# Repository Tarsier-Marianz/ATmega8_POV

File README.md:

# ATmega8-POV

A simple persistence-of-vision (POV) display with ATmega8 microcontroller

### Thanks

[KiCad IDE](http://kicad-pcb.org/) - for letting me use a free software in designing PCB

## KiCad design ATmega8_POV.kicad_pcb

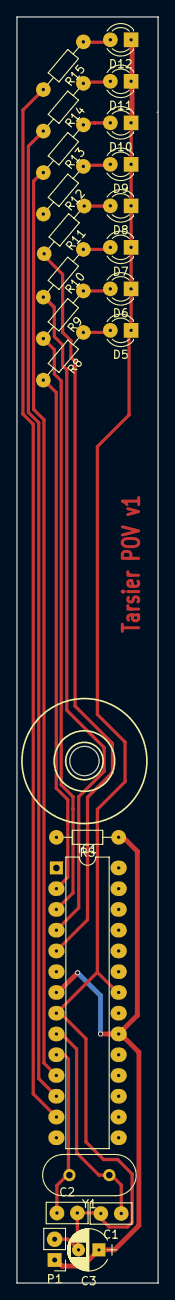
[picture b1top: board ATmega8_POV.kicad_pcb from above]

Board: 2 copper layers, 17.3 x 154.9 mm, 23 parts (0 on the bottom side), 21 nets.

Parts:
C1, C2: 22pF; C_Disc_D5.0mm_W2.5mm_P2.50mm
C3: 4.7uF; CP_Radial_D5.0mm_P2.50mm
D5, D6, D7, D8, D9, D10, D11, D12: LED; LED_D3.0mm
IC1: ATMEGA8-P; DIP-28_W7.62mm
P1: CONN_01X02; Pin_Header_Straight_1x02_Pitch2.54mm
R5: 10K; R_Axial_DIN0204_L3.6mm_D1.6mm_P7.62mm_Horizontal
R8, R9, R10, R11, R12, R13, R14, R15: 1K; R_Axial_DIN0204_L3.6mm_D1.6mm_P7.62mm_Horizontal
Y1: Crystal_Small; Crystal_HC49-4H_Vertical

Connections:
/D0: IC1.2, R8.2
/D1: IC1.3, R9.2
/D2: IC1.4, R10.2
/D3: IC1.5, R11.2
/D4: IC1.6, R12.2
/D5: IC1.11, R13.2
/D6: IC1.12, R14.2
/D7: IC1.13, R15.2
GND: C1.2, C2.2, C3.2, D5.1, D6.1, D7.1, D8.1, D9.1, D10.1, D11.1, D12.1, IC1.8, IC1.22, P1.2
unnamed: C1.1, IC1.9, Y1.1
unnamed: C2.1, IC1.10, Y1.2
unnamed: D5.2, R8.1
unnamed: D6.2, R9.1
unnamed: D7.2, R10.1
unnamed: D8.2, R11.1
unnamed: D9.2, R12.1
unnamed: D10.2, R13.1
unnamed: D11.2, R14.1
unnamed: D12.2, R15.1
unnamed: IC1.1, R5.2
VCC: C3.1, IC1.7, IC1.20, P1.1, R5.1

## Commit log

2018-02-27 Add readme additional details
2018-02-27 Fixed readme link
2018-04-05 :toilet:
2018-04-07 *changing footprints
2018-04-07 ~saving changes of schematic
2018-04-20 *readme images
